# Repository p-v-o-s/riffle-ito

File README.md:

riffle-ito
=========

The RIFFLE-ito is a lower-functionality and higher cost version of the [Riffle](http://publiclab.org/wiki/riffle) water quality sensor. The Riffle-ito is based on the Atmel328p, and is intended to be compatible with the accessibile and ubiquitous Wiring platform (and, by extension, the Arduino IDE). For a lower-cost, higher-functionalty Riffle that isn't yet compatible with Wiring, please see [here](https://github.com/bgamari/riffle). 

The width and height of the Riffle-ito device allows the device to fit through the mouth of a standard commercially produced plastic water bottle (20 mm). By inserting the Riffle-ito into such a bottle, along with a few AA batteries, and connecting a thermistor and other sensors that poke out through the water bottle cap, a very accessible water quality sensor may be constructed. 

Details:

- the Riffle-ito requires an [FTDI cable](https://www.adafruit.com/products/284) in order to be reprogrammed (e.g. Adafruit's [FTDI Friend](https://www.adafruit.com/products/284) or SparkFun's ['FTDI Basic Breakout'](https://www.sparkfun.com/products/9716)), which typically costs $15 or so. One cable can be used for several Riffle-ito senso nodes.
- includes a uSD holder, I2C EEPROM flash memory, and a high-precision real time clock (the DS3231) with coin battery backup
- programmable as an "Arduino UNO" board in the Arduino IDE
- runs at 3.3V / 16 MHz
- includes circuit for monitoring battery level
- the board width (18 mm) and height profile (uses right-angle headers) allows device to be inserted through mouth of standard plastic water bottle (one with 20 mm diameter or greater)
- Rough estimate of the total cost of parts that could be used to log temperature in a water bottle (not including shipping, the water bottle, or an FTDI cable): 38 USD;  a detailed cost estimate is [here](https://docs.google.com/spreadsheets/d/1v0O8HmP8-q_kPunHILv5Io3zThpqvPBZZoY3aYnxRDc/edit#gid=0)
- For a diagram of pin locations and optional configurations, please see this [diagram in PDF format](https://github.com/p-v-o-s/riffle328/blob/master/riffleUsage.pdf)

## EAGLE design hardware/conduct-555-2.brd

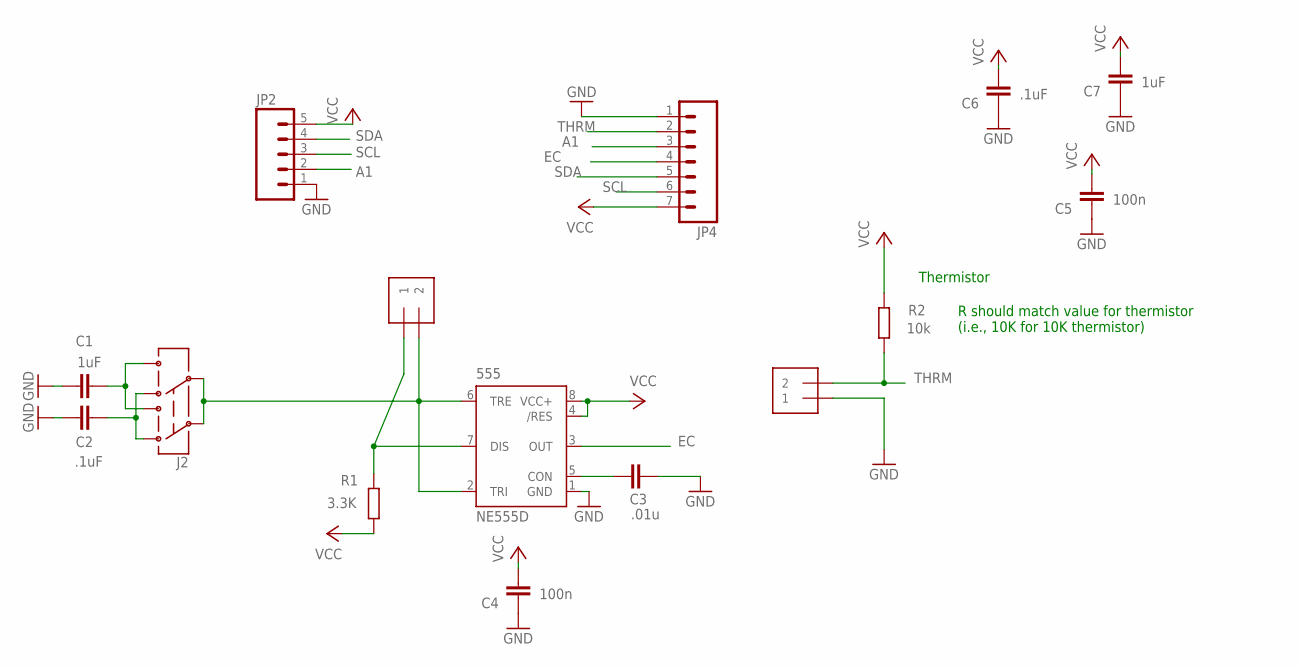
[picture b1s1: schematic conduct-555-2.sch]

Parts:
555: NE555D; SO08@1
C1, C7: 1uF; C0805
C2, C6: .1uF; C0805
C3: .01u; C0805
C4, C5: 100n; C0805
EC: 1X2-3.5MM
J2: AYZ0202
JP2: M05PTH; 1X05
JP4: M07; 1X07
R1: 3.3K; R0805
R2: 10k; R0805
THRM: 1X2-3.5MM

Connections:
A1: JP2.2, JP4.3
EC: 555.3 (OUT), JP4.4
GND: 555.1 (GND), C1.2, C2.2, C3.1, C4.1, C5.1, C6.1, C7.1, JP2.1, JP4.1, THRM.1
N1: 555.2 (TRI), 555.6 (TRE), EC.2, J2.2, J2.5
unnamed: 555.5 (CON), C3.2
unnamed: 555.7 (DIS), EC.1, R1.2
unnamed: C2.1, J2.3 (1), J2.6 (4)
SCL: JP2.3, JP4.6
SDA: JP2.4, JP4.5
THRM: JP4.2, R2.1, THRM.2
VCC: 555.4 (/RES), 555.8 (VCC+), C4.2, C5.2, C6.2, C7.2, JP2.5, JP4.7, R1.1, R2.2
VDD2: C1.1, J2.1 (3), J2.4 (6)

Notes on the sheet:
Thermistor
R should match value for thermistor (i.e., 10K for 10K thermistor)

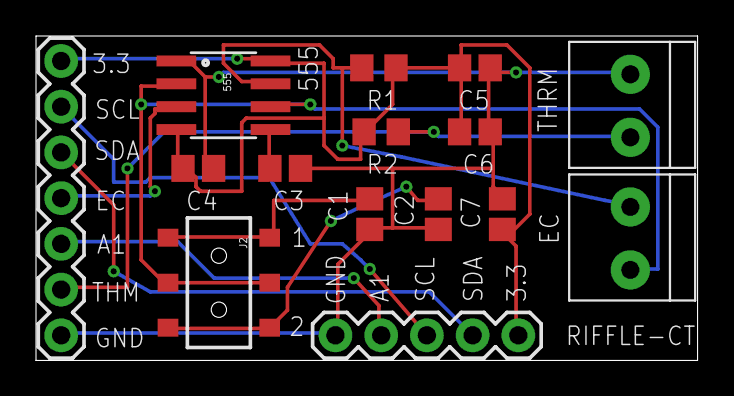
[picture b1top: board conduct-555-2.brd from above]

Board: 2 copper layers, 36.8 x 18.0 mm, 15 parts (0 on the bottom side), 12 nets.

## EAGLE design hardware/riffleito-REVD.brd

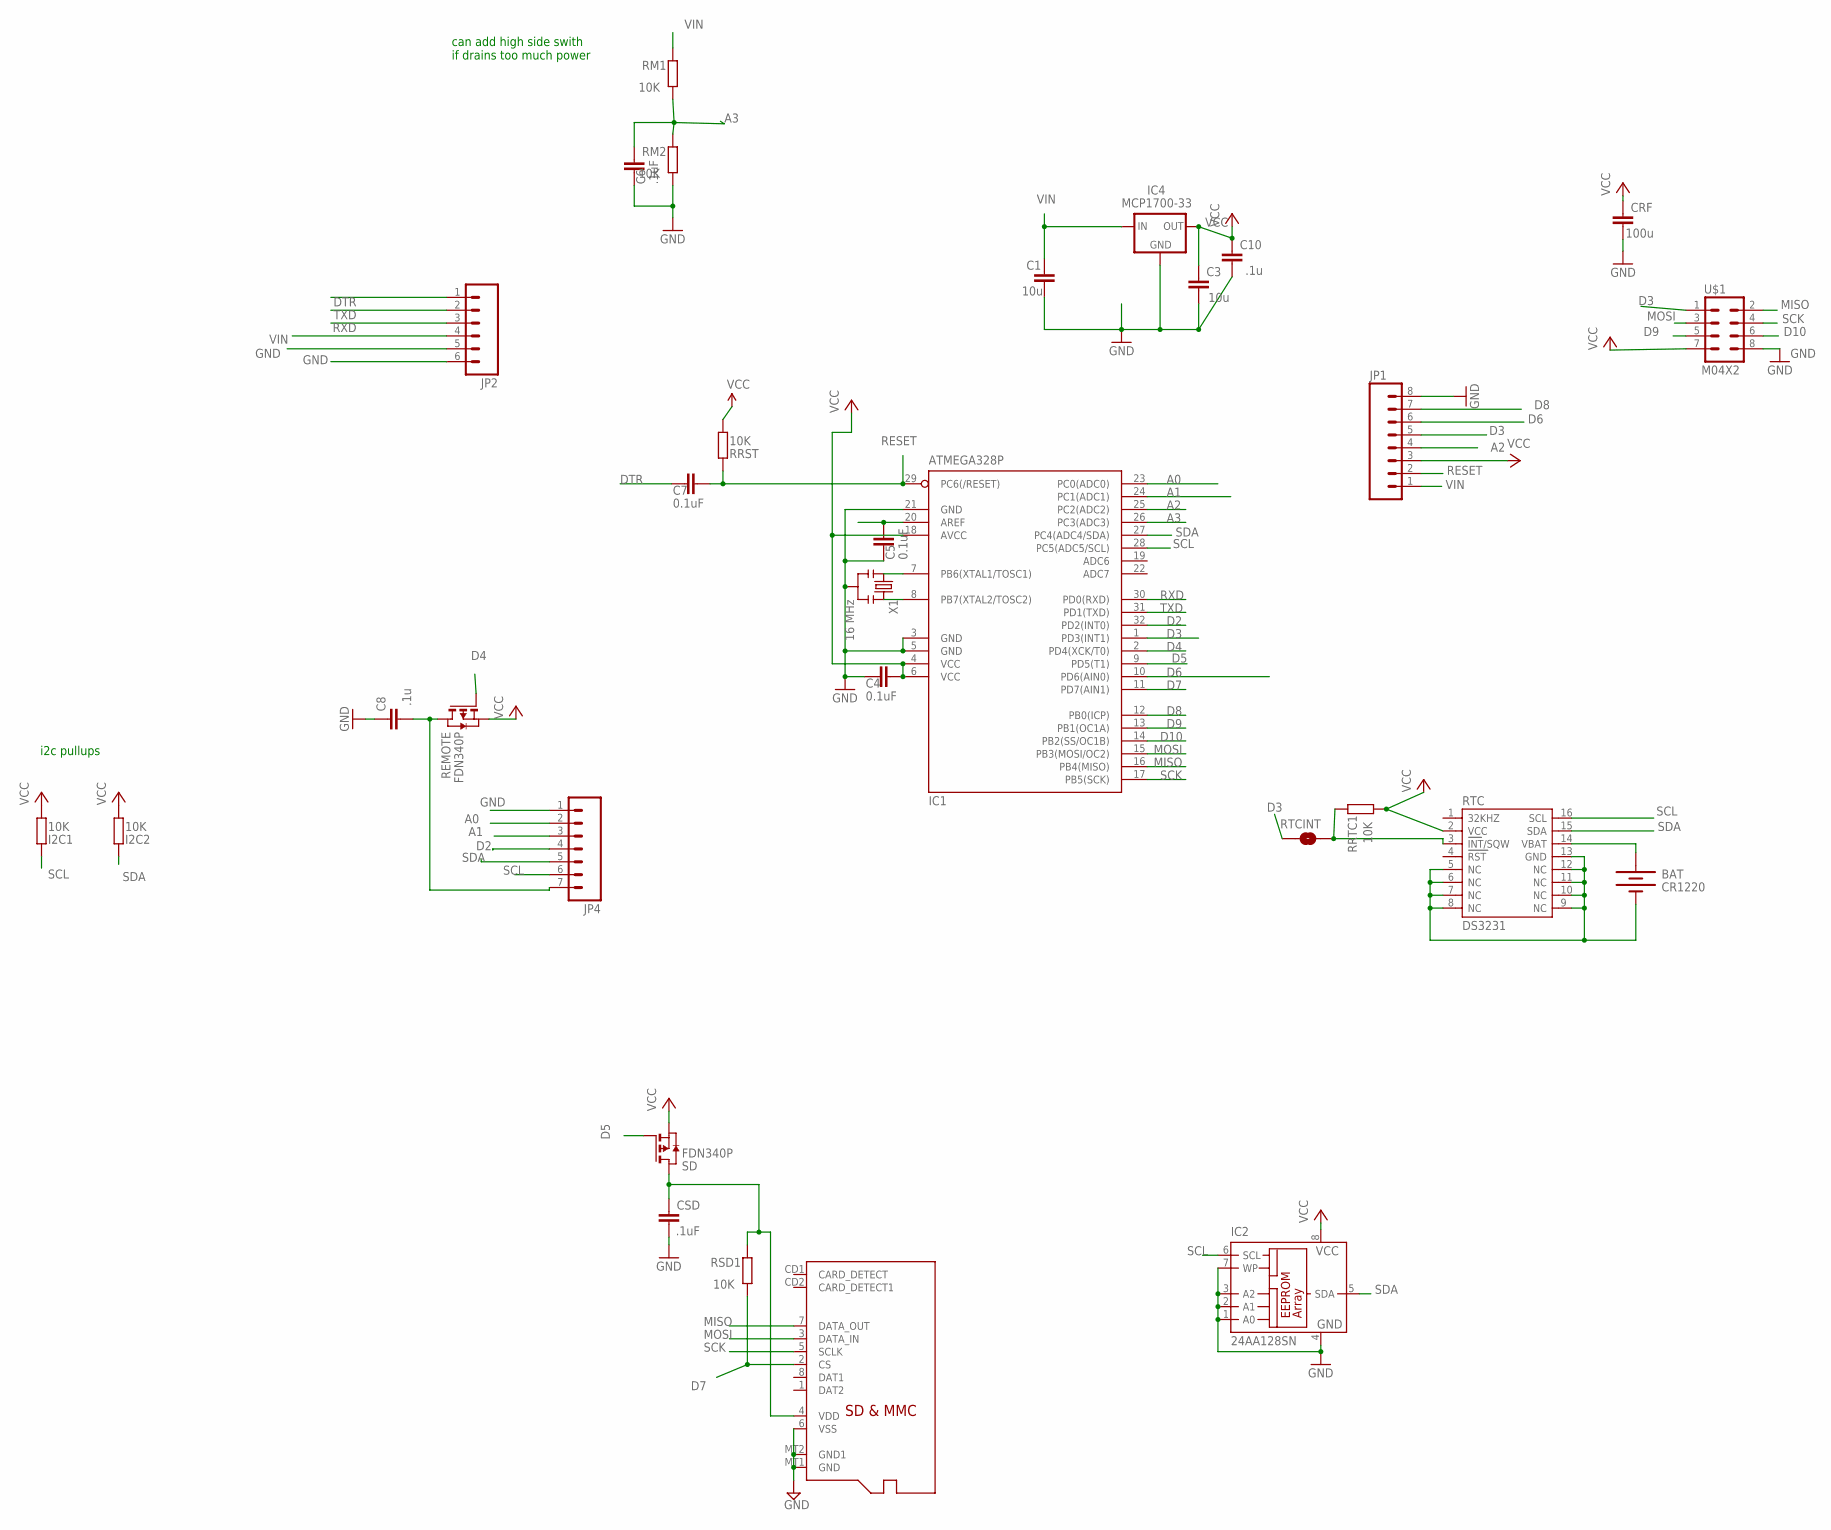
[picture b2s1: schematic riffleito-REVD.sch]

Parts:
BAT: CR1220; BATTCON_12MM_SMT
C1, C3: 10u; C0805
C4, C5, C7: 0.1uF; C0805@1
C6: .1uF; C0805@1
C8, C10: .1u; C0805
CRF: 100u; C0805
CSD: .1uF; C0805
I2C1, I2C2: 10K; R0805
IC1: ATMEGA328P; TQFP32-08
IC2: 24AA128SN; SO-08
IC4: MCP1700-33; SOT23
JP1: M081X08; 1X08
JP2: M06SIP; 1X06
JP4: M07; 1X07
MICROSD: MICROSD
REMOTE: FDN340P; SOT-23
RM1, RM2: 10K; R0805
RRST: 10K; R0805
RRTC1: 10K; R0805
RSD1: 10K; R0805
RTC: DS3231
RTCINT: SOLDERJUMPERNO; SJ_2S-NO
SD: FDN340P; SOT-23
U$1: M04X2; 2X4
X1: 16 MHz; RESONATOR-SMD

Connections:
A0: IC1.23 (PC0(ADC0)), JP4.2
A1: IC1.24 (PC1(ADC1)), JP4.3
A2: IC1.25 (PC2(ADC2)), JP1.4
A3: C6.2, IC1.26 (PC3(ADC3)), RM1.1, RM2.2
AREF: C5.2, IC1.20 (AREF)
D2: IC1.32 (PD2(INT0)), JP4.4
D3: IC1.1 (PD3(INT1)), JP1.5, RTCINT.2, U$1.1
D4: IC1.2 (PD4(XCK/T0)), REMOTE.3 (G)
D5: IC1.9 (PD5(T1)), SD.3 (G)
D6: IC1.10 (PD6(AIN0)), JP1.6
D7: IC1.11 (PD7(AIN1)), MICROSD.2 (CS), RSD1.1
D8: IC1.12 (PB0(ICP)), JP1.7
D9: IC1.13 (PB1(OC1A)), U$1.5
D10: IC1.14 (PB2(SS/OC1B)), U$1.6
DTR: C7.1, JP2.1
GND: BAT.P$1 (-), C1.2, C3.2, C4.1, C5.1, C6.1, C8.1, C10.2, CRF.2, CSD.2, IC1.3 (GND), IC1.5 (GND), IC1.21 (GND), IC2.1 (A0), IC2.2 (A1), IC2.3 (A2), IC2.4 (GND), IC2.7 (WP), IC4.1 (GND), JP1.8, JP2.5, JP2.6, JP4.1, MICROSD.6 (VSS), MICROSD.MT1 (GND), MICROSD.MT2 (GND1), RM2.1, RTC.5 (NC), RTC.6 (NC), RTC.7 (NC), RTC.8 (NC), RTC.9 (NC), RTC.10 (NC), RTC.11 (NC), RTC.12 (NC), RTC.13 (GND), U$1.8, X1.2
MISO: IC1.16 (PB4(MISO)), MICROSD.7 (DATA_OUT), U$1.2
MOSI: IC1.15 (PB3(MOSI/OC2)), MICROSD.3 (DATA_IN), U$1.3
unnamed: RRTC1.2, RTC.3 (INT/SQW), RTCINT.1
unnamed: IC1.8 (PB7(XTAL2/TOSC2)), X1.3
unnamed: IC1.7 (PB6(XTAL1/TOSC1)), X1.1
unnamed: C8.2, JP4.7, REMOTE.1 (D)
RESET: C7.2, IC1.29 (PC6(/RESET)), JP1.2, RRST.2
RTC_BATT: BAT.P$2 (+), RTC.14 (VBAT)
RXD: IC1.30 (PD0(RXD)), JP2.3
SCK: IC1.17 (PB5(SCK)), MICROSD.5 (SCLK), U$1.4
SCL: I2C1.2, IC1.28 (PC5(ADC5/SCL)), IC2.6 (SCL), JP4.6, RTC.16 (SCL)
SDA: I2C2.2, IC1.27 (PC4(ADC4/SDA)), IC2.5 (SDA), JP4.5, RTC.15 (SDA)
TXD: IC1.31 (PD1(TXD)), JP2.2
VCC: C3.1, C4.2, C10.1, CRF.1, I2C1.1, I2C2.1, IC1.4 (VCC), IC1.6 (VCC), IC1.18 (AVCC), IC2.8 (VCC), IC4.2 (OUT), JP1.3, REMOTE.2 (S), RRST.1, RRTC1.1, RTC.2 (VCC), SD.2 (S), U$1.7
VDD: CSD.1, MICROSD.4 (VDD), RSD1.2, SD.1 (D)
VIN: C1.1, IC4.3 (IN), JP1.1, JP2.4, RM1.2

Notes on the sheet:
can add high side swith if drains too much power
i2c pullups

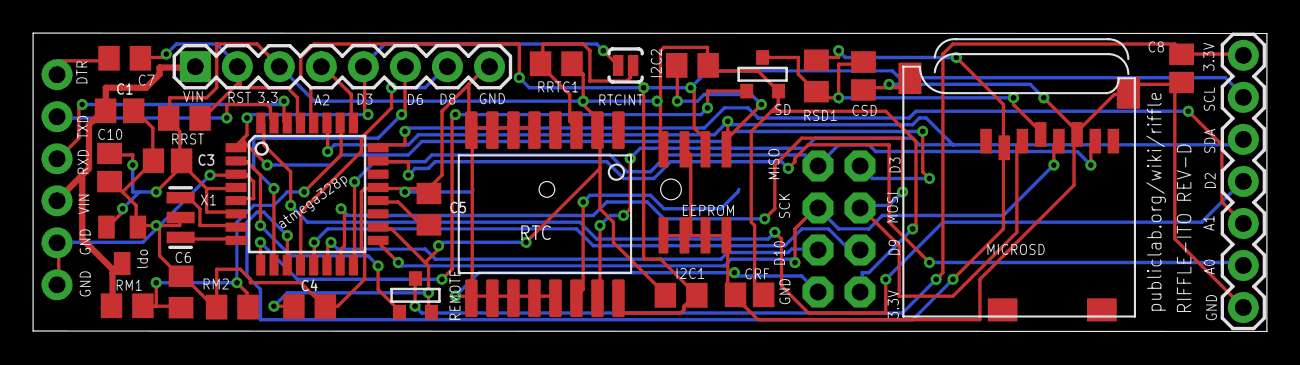
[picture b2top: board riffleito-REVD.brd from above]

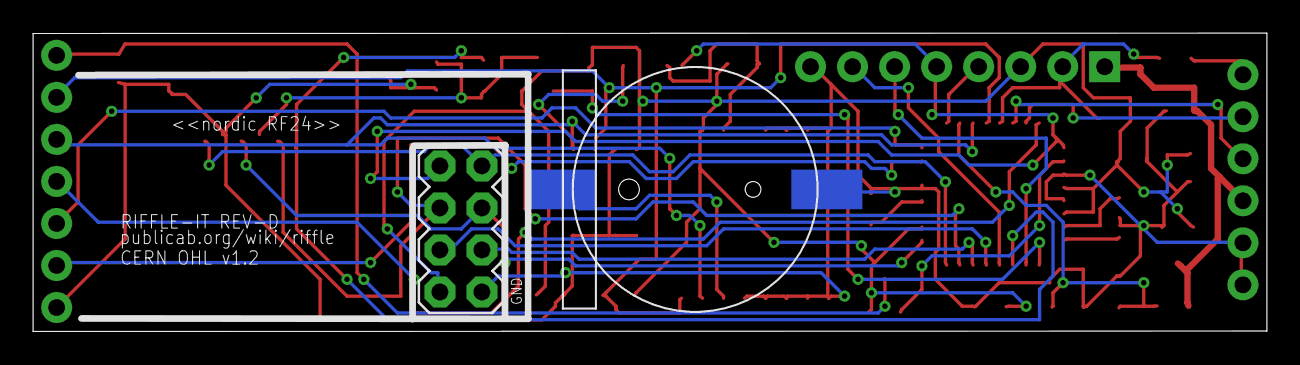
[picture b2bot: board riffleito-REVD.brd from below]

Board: 2 copper layers, 74.6 x 18.0 mm, 31 parts (2 on the bottom side), 32 nets.

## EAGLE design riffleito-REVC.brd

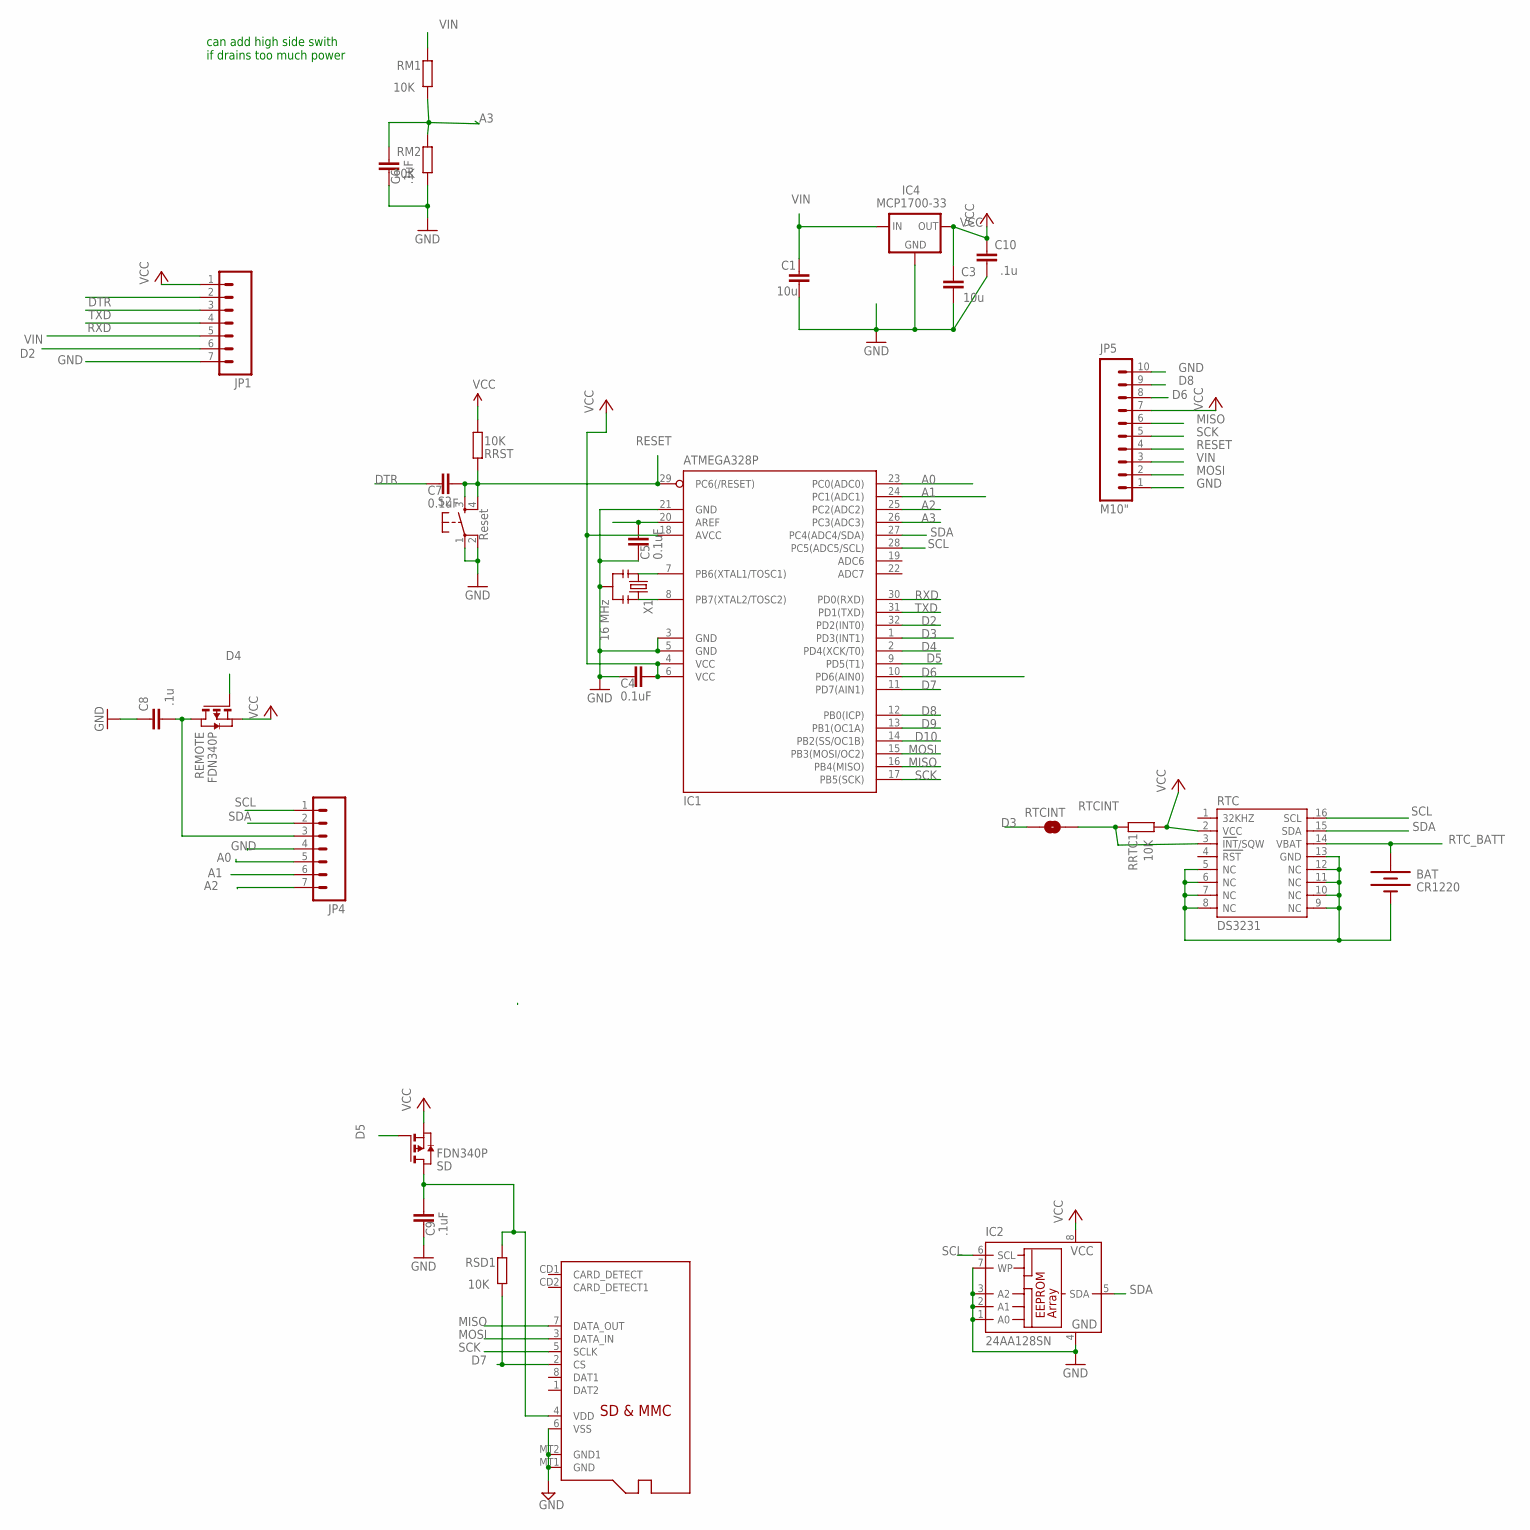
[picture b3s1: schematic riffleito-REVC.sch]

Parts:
BAT: CR1220; BATTCON_12MM_SMT
C1, C3: 10u; C0805
C4, C5, C7: 0.1uF; C0805@1
C6, C9: .1uF; C0805@1
C8, C10: .1u; C0805
IC1: ATMEGA328P; TQFP32-08
IC2: 24AA128SN; SO-08
IC4: MCP1700-33; SOT23
JP1, JP4: M07; 1X07
JP5: M10"; 1X10
MICROSD: MICROSD
REMOTE: FDN340P; SOT-23
RM1, RM2: 10K; R0805
RRST: 10K; R0805
RRTC1: 10K; R0805
RSD1: 10K; R0805
RTC: DS3231
RTCINT: SOLDERJUMPERNO; SJ_2S-NO
S2: Reset; TACTILE_SWITCH_SMD
SD: FDN340P; SOT-23
X1: 16 MHz; RESONATOR-SMD

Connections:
A0: IC1.23 (PC0(ADC0)), JP4.5
A1: IC1.24 (PC1(ADC1)), JP4.6
A2: IC1.25 (PC2(ADC2)), JP4.7
A3: C6.2, IC1.26 (PC3(ADC3)), RM1.1, RM2.2
AREF: C5.2, IC1.20 (AREF)
D2: IC1.32 (PD2(INT0)), JP1.6
D3: IC1.1 (PD3(INT1)), RTCINT.2
D4: IC1.2 (PD4(XCK/T0)), REMOTE.3 (G)
D5: IC1.9 (PD5(T1)), SD.3 (G)
D6: IC1.10 (PD6(AIN0)), JP5.8
D7: IC1.11 (PD7(AIN1)), MICROSD.2 (CS), RSD1.1
D8: IC1.12 (PB0(ICP)), JP5.9
D9: IC1.13 (PB1(OC1A))
D10: IC1.14 (PB2(SS/OC1B))
DTR: C7.1, JP1.2
GND: BAT.P$1 (-), C1.2, C3.2, C4.1, C5.1, C6.1, C8.1, C9.1, C10.2, IC1.3 (GND), IC1.5 (GND), IC1.21 (GND), IC2.1 (A0), IC2.2 (A1), IC2.3 (A2), IC2.4 (GND), IC2.7 (WP), IC4.1 (GND), JP1.7, JP4.4, JP5.1, JP5.10, MICROSD.6 (VSS), MICROSD.MT1 (GND), MICROSD.MT2 (GND1), RM2.1, RTC.5 (NC), RTC.6 (NC), RTC.7 (NC), RTC.8 (NC), RTC.9 (NC), RTC.10 (NC), RTC.11 (NC), RTC.12 (NC), RTC.13 (GND), S2.1, S2.2, X1.2
MISO: IC1.16 (PB4(MISO)), JP5.6, MICROSD.7 (DATA_OUT)
MOSI: IC1.15 (PB3(MOSI/OC2)), JP5.2, MICROSD.3 (DATA_IN)
unnamed: IC1.8 (PB7(XTAL2/TOSC2)), X1.3
unnamed: IC1.7 (PB6(XTAL1/TOSC1)), X1.1
RESET: C7.2, IC1.29 (PC6(/RESET)), JP5.4, RRST.2, S2.3, S2.4
RTCINT: RRTC1.2, RTC.3 (INT/SQW), RTCINT.1
RTC_BATT: BAT.P$2 (+), RTC.14 (VBAT)
RXD: IC1.30 (PD0(RXD)), JP1.4
SCK: IC1.17 (PB5(SCK)), JP5.5, MICROSD.5 (SCLK)
SCL: IC1.28 (PC5(ADC5/SCL)), IC2.6 (SCL), JP4.1, RTC.16 (SCL)
SDA: IC1.27 (PC4(ADC4/SDA)), IC2.5 (SDA), JP4.2, RTC.15 (SDA)
TXD: IC1.31 (PD1(TXD)), JP1.3
VCC: C3.1, C4.2, C8.2, C10.1, IC1.4 (VCC), IC1.6 (VCC), IC1.18 (AVCC), IC2.8 (VCC), IC4.2 (OUT), JP1.1, JP4.3, JP5.7, REMOTE.1 (D), REMOTE.2 (S), RRST.1, RRTC1.1, RTC.2 (VCC), SD.2 (S)
VDD: C9.2, MICROSD.4 (VDD), RSD1.2, SD.1 (D)
VIN: C1.1, IC4.3 (IN), JP1.5, JP5.3, RM1.2

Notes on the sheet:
can add high side swith if drains too much power

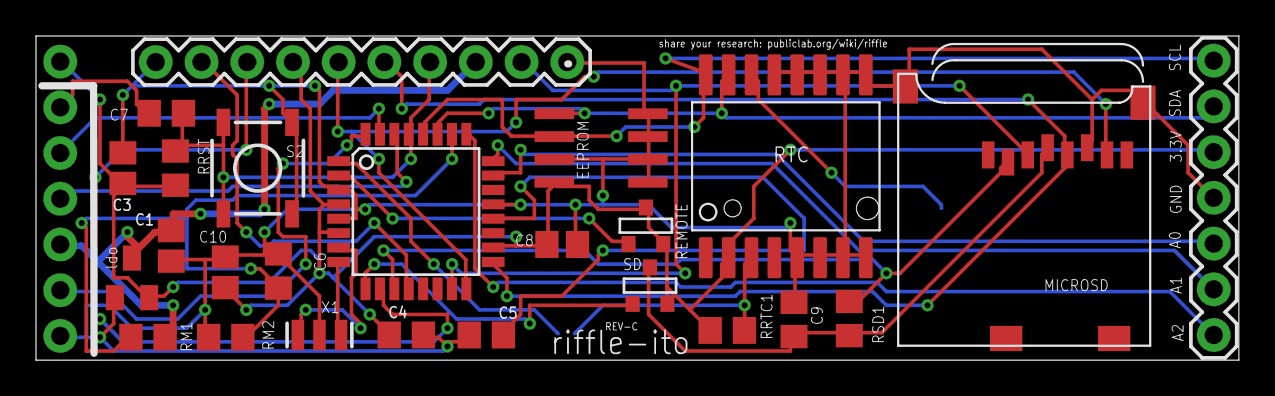
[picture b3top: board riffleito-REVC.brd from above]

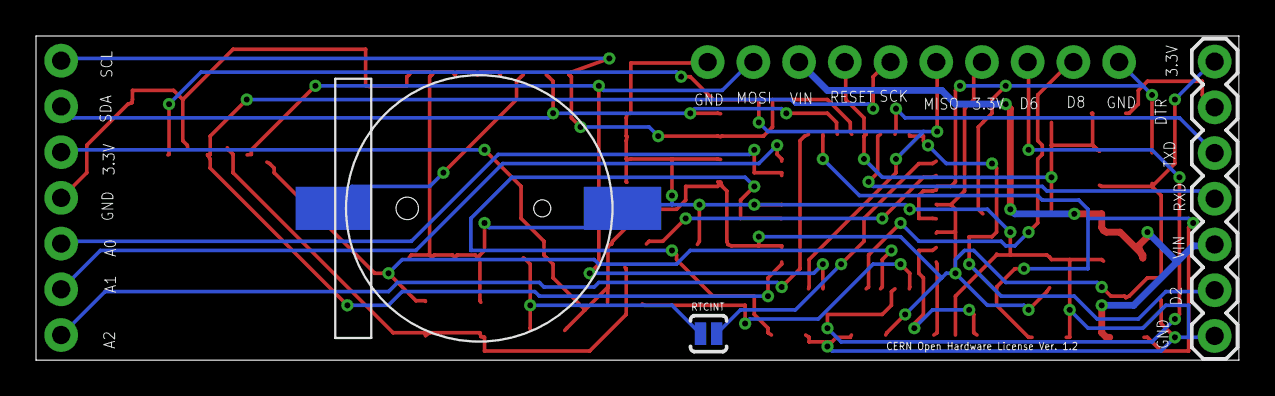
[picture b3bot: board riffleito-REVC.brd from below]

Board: 2 copper layers, 66.8 x 18.0 mm, 28 parts (3 on the bottom side), 29 nets.

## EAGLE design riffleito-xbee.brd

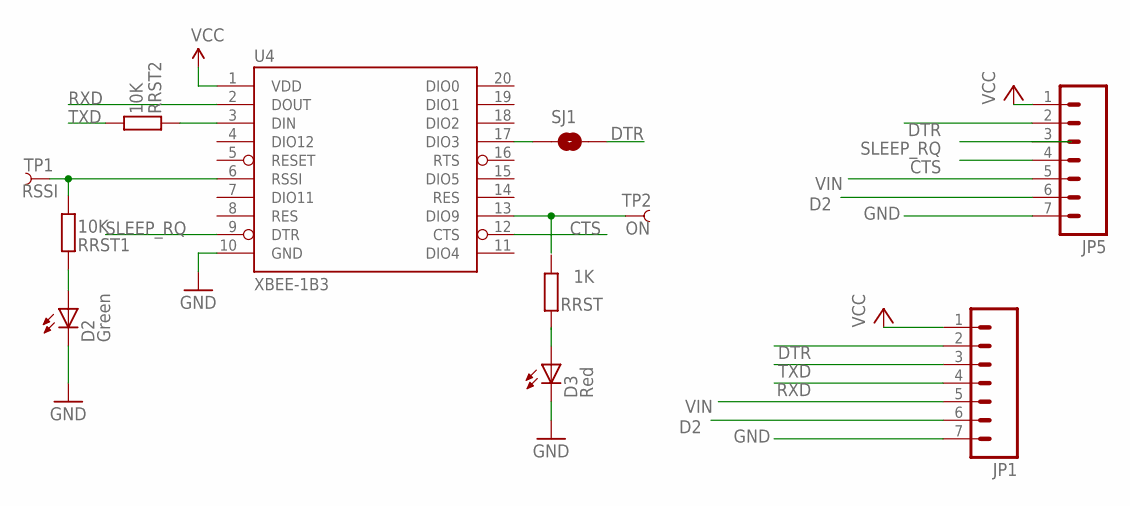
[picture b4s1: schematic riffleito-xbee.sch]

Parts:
D2: Green; LED-0603
D3: Red; LED-0603
JP1, JP5: M07; 1X07
RRST: 1K; R0805
RRST1, RRST2: 10K; R0805
SJ1: SOLDERJUMPERNC; SJ_2S
TP1: RSSI; PAD.03X.05
TP2: ON; PAD.03X.05
U4: XBEE-1B3; XBEE-SMD

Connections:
CTS: JP5.4, U4.12 (CTS)
D2: JP1.6, JP5.6
DTR: JP1.2, JP5.2, SJ1.2
GND: D2.C, D3.C, JP1.7, JP5.7, U4.10 (GND)
unnamed: TP2.P$1, U4.13 (DIO9)
unnamed: D2.A, RRST1.2
unnamed: RRST1.1, TP1.P$1, U4.6 (RSSI)
unnamed: D3.A, RRST.2
unnamed: RRST2.2, U4.3 (DIN)
unnamed: SJ1.1, U4.17 (DIO3)
RXD: JP1.4, U4.2 (DOUT)
SLEEP_RQ: JP5.3, U4.9 (DTR)
TXD: JP1.3, RRST2.1
VCC: JP1.1, JP5.1, U4.1 (VDD)
VIN: JP1.5, JP5.5

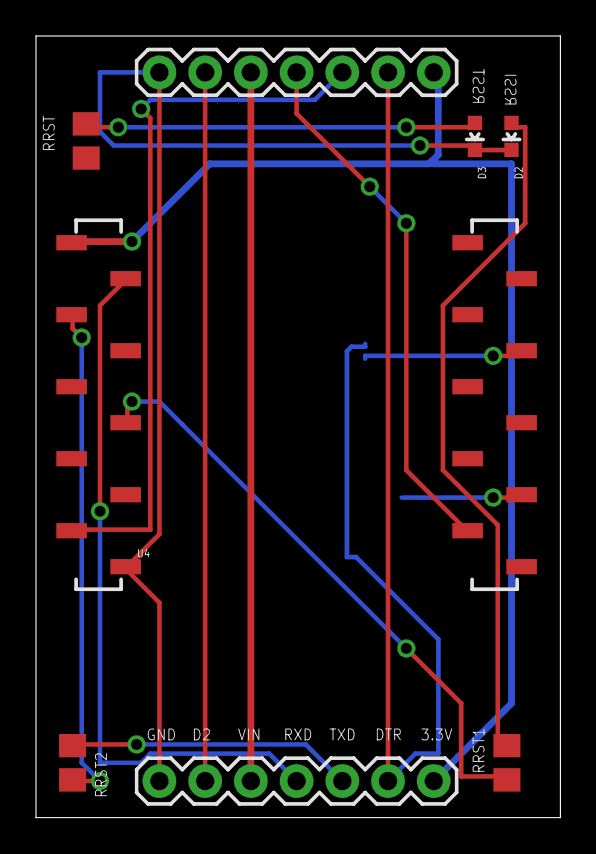
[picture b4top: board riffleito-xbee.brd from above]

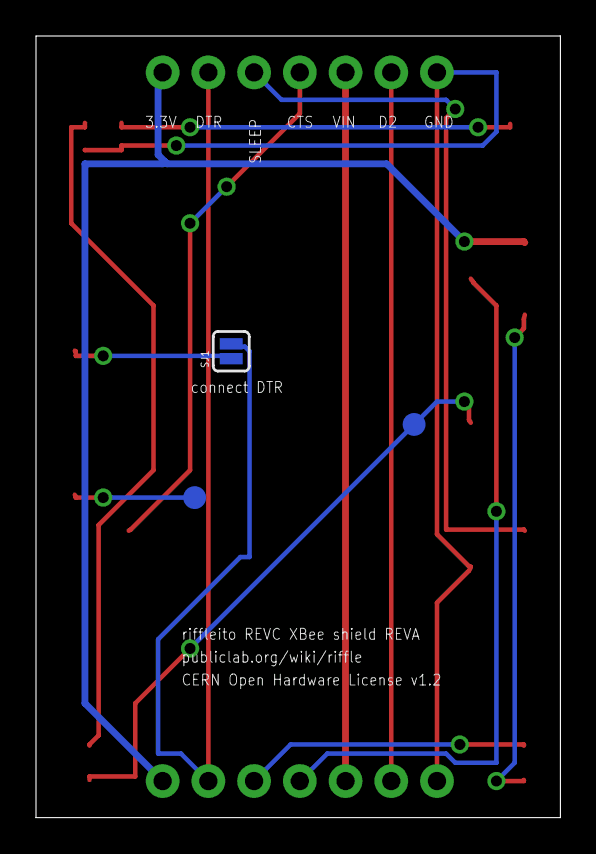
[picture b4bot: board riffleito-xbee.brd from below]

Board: 2 copper layers, 29.1 x 43.4 mm, 11 parts (3 on the bottom side), 15 nets.

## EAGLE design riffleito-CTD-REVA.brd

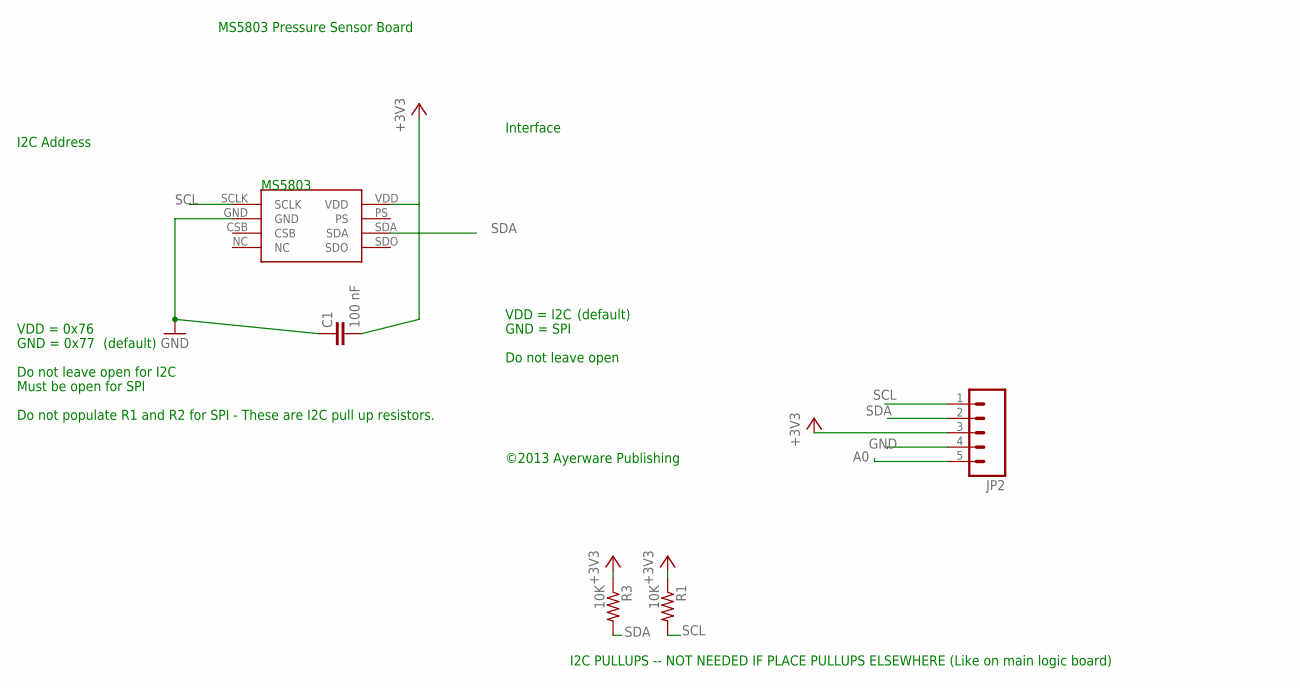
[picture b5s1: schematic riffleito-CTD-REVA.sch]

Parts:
C1: 100 nF; 0402-CAP
JP2: M05PTH; 1X05
MS5803: MS5803-14BA
R1, R3: 10K; 0402-RES

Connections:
+3V3: C1.1, JP2.3, MS5803.VDD, R1.1, R3.1
A0: JP2.5
GND: C1.2, JP2.4, MS5803.GND
SCL: JP2.1, MS5803.SCLK, R1.2
SDA: JP2.2, MS5803.SDA, R3.2

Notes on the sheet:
I2C Address
GND = 0x77
Interface
VDD = I2C
VDD = 0x76
GND = SPI
Do not leave open for I2C
Do not leave open
Must be open for SPI
MS5803
©2013 Ayerware Publishing
MS5803 Pressure Sensor Board
Do not populate R1 and R2 for SPI - These are I2C pull up resistors.
(default)
I2C PULLUPS -- NOT NEEDED IF PLACE PULLUPS ELSEWHERE (Like on main logic board)

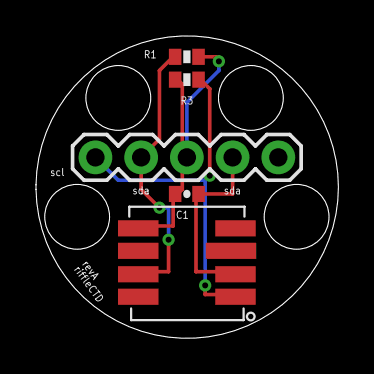
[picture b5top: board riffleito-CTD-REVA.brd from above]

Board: 2 copper layers, 16.8 x 16.8 mm, 5 parts (0 on the bottom side), 4 nets.

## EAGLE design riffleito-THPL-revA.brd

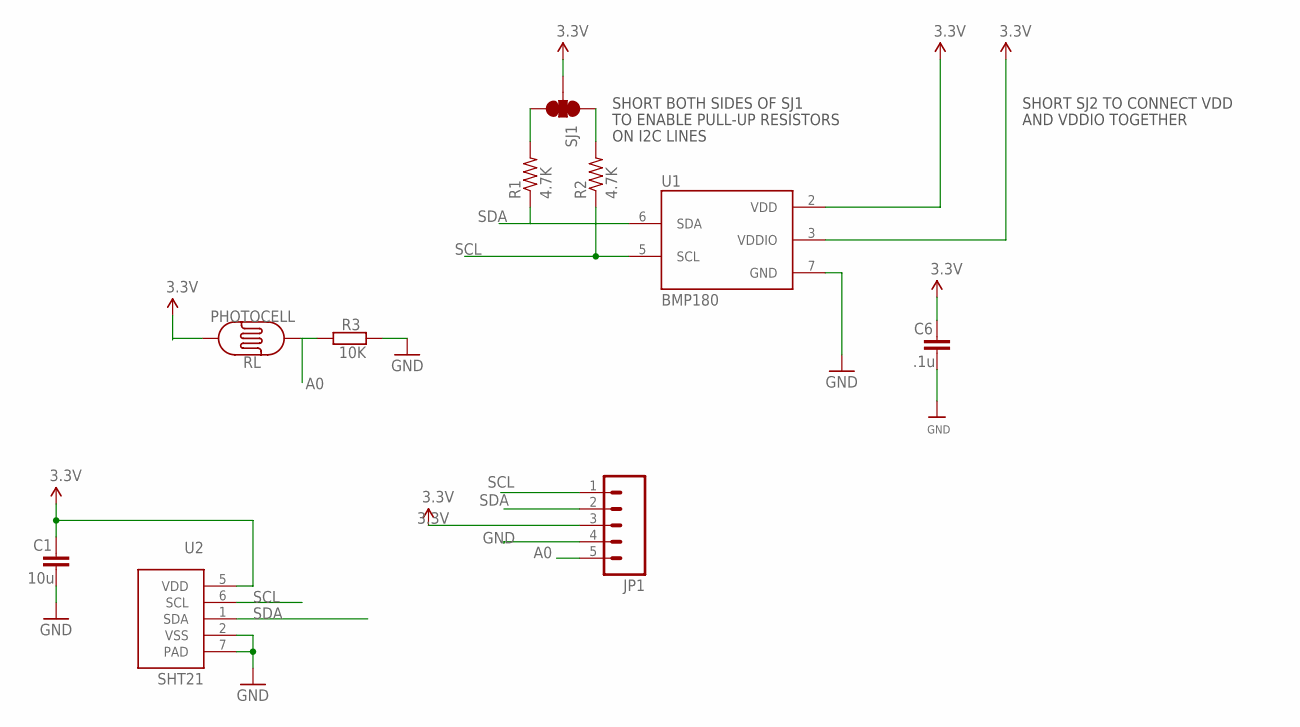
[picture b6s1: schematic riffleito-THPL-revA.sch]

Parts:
C1: 10u; C0805
C6: .1u; C0805
JP1: M05PTH; 1X05
R1, R2: 4.7K; 0603-RES
R3: 10K; R0805
RL: PHOTOCELL
SJ1: SOLDERJUMPER_2WAYPASTE1&2&3; SJ_3_PASTE1&2&3
U1: BMP180
U2: SHT21; SEN-SENSIRION-SHT2X

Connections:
3.3V: C1.1, C6.1, JP1.3, RL.2, SJ1.2, U1.2 (VDD), U1.3 (VDDIO), U2.5 (VDD)
A0: JP1.5, R3.1, RL.1
GND: C1.2, C6.2, JP1.4, R3.2, U1.7 (GND), U2.2 (VSS), U2.7 (PAD)
unnamed: R1.2, SJ1.3
unnamed: R2.2, SJ1.1
SCL: JP1.1, R2.1, U1.5 (SCL), U2.6 (SCL)
SDA: JP1.2, R1.1, U1.6 (SDA), U2.1 (SDA)

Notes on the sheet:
SHORT BOTH SIDES OF SJ1
TO ENABLE PULL-UP RESISTORS
ON I2C LINES
SHORT SJ2 TO CONNECT VDD
AND VDDIO TOGETHER

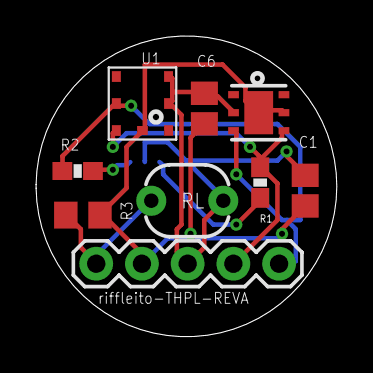
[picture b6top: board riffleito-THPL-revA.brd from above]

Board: 2 copper layers, 16.7 x 16.7 mm, 10 parts (1 on the bottom side), 7 nets.

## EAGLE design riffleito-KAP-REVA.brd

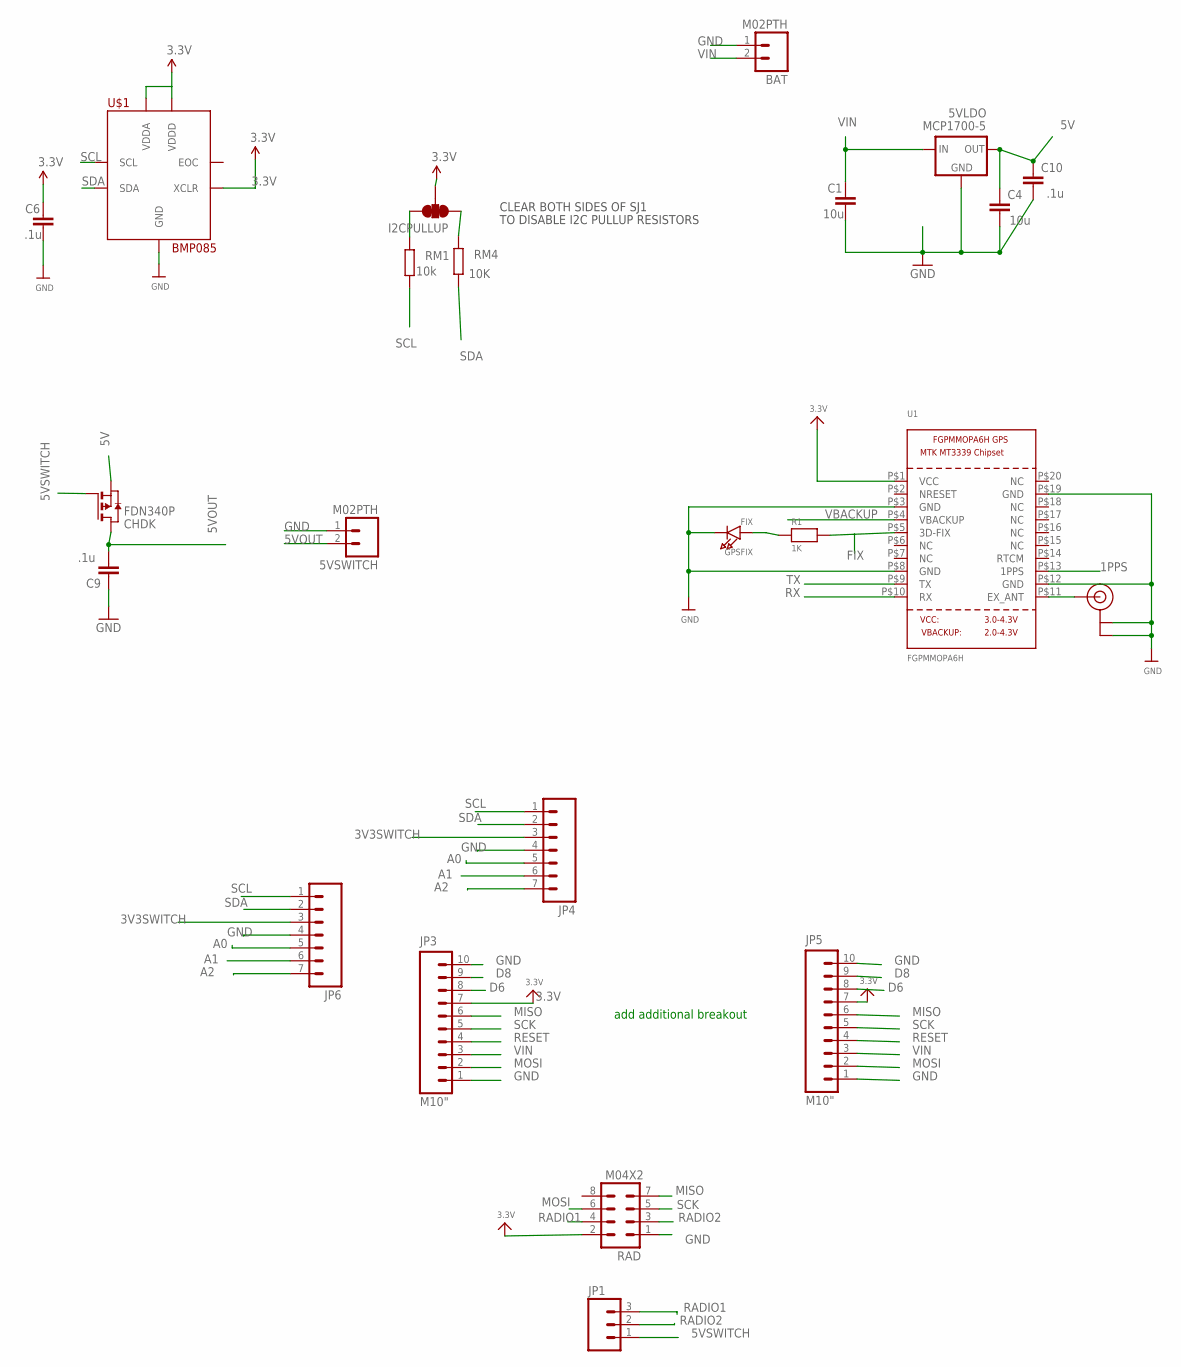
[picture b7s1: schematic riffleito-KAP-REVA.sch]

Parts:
5VLDO: MCP1700-5; SOT23
5VSWITCH: M02PTH; 1X02
BAT: M02PTH; 1X02
C1, C4: 10u; C0805
C6, C9, C10: .1u; C0805
CHDK: FDN340P; SOT-23
GPSFIX: FIX; CHIPLED_0805
I2CPULLUP: SOLDERJUMPER_2WAYPASTE1&2&3; SJ_3_PASTE1&2&3
JP1: M03PTH; 1X03
JP3, JP5: M10"; 1X10
JP4, JP6: M07; 1X07
R1: 1K; 0805
RAD: M04X2; 2X4
RM1: 10k; R0805
RM4: 10K; R0805
U1: FGPMMOPA6H
U$1: BMP085
U$20: U.FL

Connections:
1PPS: U1.P$13 (1PPS)
3.3V: C6.1, I2CPULLUP.2, JP3.7, JP5.7, RAD.2, U1.P$1 (VCC), U$1.P$3 (VDDA), U$1.P$4 (VDDD), U$1.P$8 (XCLR)
3V3SWITCH: JP4.3, JP6.3
5V: 5VLDO.2 (OUT), C4.1, C10.1, CHDK.2 (S)
5VOUT: 5VSWITCH.2, C9.2, CHDK.1 (D)
5VSWITCH: CHDK.3 (G), JP1.1
A0: JP4.5, JP6.5
A1: JP4.6, JP6.6
A2: JP4.7, JP6.7
D6: JP3.8, JP5.8
D8: JP3.9, JP5.9
GND: 5VLDO.1 (GND), 5VSWITCH.1, BAT.1, C1.2, C4.2, C6.2, C9.1, C10.2, GPSFIX.C, JP3.1, JP3.10, JP4.4, JP5.1, JP5.10, JP6.4, RAD.1, U1.P$3 (GND), U1.P$8 (GND), U1.P$12 (GND), U1.P$19 (GND), U$1.P$1 (GND), U$20.P$1 (GND), U$20.P$2 (GND)
MISO: JP3.6, JP5.6, RAD.7
MOSI: JP3.2, JP5.2, RAD.6
unnamed: GPSFIX.A, R1.1
unnamed: R1.2, U1.P$5 (3D-FIX)
unnamed: I2CPULLUP.3, RM1.2
unnamed: U1.P$11 (EX_ANT), U$20.P$3 (SIGNAL)
unnamed: I2CPULLUP.1, RM4.2
RADIO1: JP1.3, RAD.4
RADIO2: JP1.2, RAD.3
RESET: JP3.4, JP5.4
RX: U1.P$10 (RX)
SCK: JP3.5, JP5.5, RAD.5
SCL: JP4.1, JP6.1, RM1.1, U$1.P$6 (SCL)
SDA: JP4.2, JP6.2, RM4.1, U$1.P$7 (SDA)
TX: U1.P$9 (TX)
VBACKUP: U1.P$4 (VBACKUP)
VIN: 5VLDO.3 (IN), BAT.2, C1.1, JP3.3, JP5.3

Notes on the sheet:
CLEAR BOTH SIDES OF SJ1
TO DISABLE I2C PULLUP RESISTORS
add additional breakout

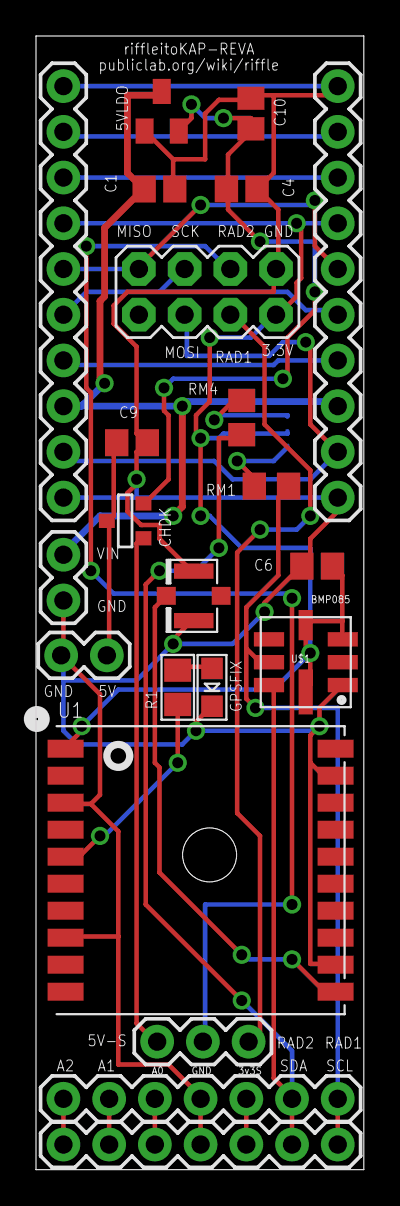
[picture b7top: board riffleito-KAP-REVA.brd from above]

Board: 2 copper layers, 18.2 x 63.0 mm, 23 parts (1 on the bottom side), 25 nets.

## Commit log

2014-06-26 added
2014-06-26 routed!
2014-06-26 update - routed
2014-06-27 datasheet for nordic 2.4GHz radio
2014-06-27 friendly tutorial for nordic 2.4GHz radio
2014-06-27 reorg files

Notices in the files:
hardware/conduct-555-2.brd:
CERN OHL v1.2
riffleito-REVC.brd:
CERN Open Hardware License Ver. 1.2
riffleito-xbee.brd:
CERN Open Hardware License v1.2
parts and their libraries:
SparkFun-AnalogIC: Licensing:Creative Commons ShareAlike 4.0 International - https://creativecommons.org/licenses/by-sa/4.0
SparkFun-Sensors: Licensing: CC v3.0 Share-Alike You are welcome to use this library for commercial purposes.
